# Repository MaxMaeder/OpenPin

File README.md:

# OpenPin

OpenPin is an open-source project which lets you use your Ai Pin after Humane bricked them. You can install it in a few clicks & without any ADB certs!

## Installing OpenPin

Please see [OpenPin.org](https://openpin.org) for installation and usage instructions.

## Building a Interposer

### Bill of Materials

| Qty | Name              | Where to Buy                                      |
| --- | ----------------- | ------------------------------------------------- |
| 4   | M2x8mm Hex Screws | [Amazon](https://www.amazon.com/dp/B094NVN97P)    |
| 4   | M2 Hex Locknuts   | [Amazon](https://www.amazon.com/dp/B07L2W3QX3)    |
| 4   | Small Magnets     | [Amazon](https://www.amazon.com/dp/B0936M3WPK)    |
| 1   | Micro-USB Port    | [DigiKey](https://www.digikey.com/short/t2z9zr7h) |
| 1   | Pogo-Pin Assembly | [DigiKey](https://www.digikey.com/short/dm33vmd2) |

If you order the PCB with the USB-port already soldered (as in the instructions below) you do **NOT** need to buy the 'Micro-USB Port' part.

### Tools Required

| Name                | Where to Buy                                   |
| ------------------- | ---------------------------------------------- |
| 1.5mm Hex Driver    | Inc. with Screws                               |
| 4mm Nut Driver      | [Amazon](https://www.amazon.com/dp/B0009OIJMI) |
| T27 TORX Hex Driver | [Amazon](https://www.amazon.com/dp/B005G3B4MO) |

You will also need soldering tools and a 3D printer, depending on how much you choose to do yourself (versus using a service).

1. Order the PCBs

The following instructions are for if you want to buy the PCBs with the surface mount USB port already soldered.

> These instructions are for JLCPCB. I don't have any affiliation, I just like them.

**Upload gerbers**

- Download the [pin-interposer.zip](interposer/pcb/production/pin-interposer.zip) (the zipped Gerber files)
- Take `pin-interposer.zip`, go to [JLCPCB.com](https://jlcpcb.com), and simply upload into the file dropbox

**Set PCB details**

- The only setting you need to change is toggling on 'PCB Assembly'
- Click next, confirm you see the PCB in the preview, then click next again

**Upload assembly files**

- Download [bom.csv](interposer/pcb/production/bom.csv) and [positions.csv](interposer/pcb/production/positions.csv)
- Upload `bom.csv` into the left dropbox & `positions.csv` into the right, then click next

**Set parts to assemble**

- Click the search icon across from J1, enter `10118193-0001LF`, and search & select it
- Leave the other rows alone
- Click next, it will ask if you are sure you don't want to assemble the other rows, click confirm

**Click through rest of process and check out!**

2. 3D-print plastic parts

- Download the two 3D models: [Pin-Base.stl](interposer/prints/production/Pin-Base.stl) and [Pin-Cradle.stl](interposer/prints/production/Pin-Cradle.stl)
- Print with 0.2mm quality or better in PLA

3. Solder the pogo-pins

- Push the pins of the part into the 4 matching holes on the board<br>
  **Make sure the part is on the same face of the board as the USB port!**
- Solder one pin to start with, make sure its flush with the board and perfectly vertical<br>
  _If not soldered correctly, reheat the solder joint and adjust._
- Solder the remaining pins

4. Final assembly

**Putting the parts together**

- Put the Pin Base down on a table
- Press the PCB into the matching recess (it should be fairly obvious how it fits)
- Place the Pin Cradle overtop of this assembly, aligning it so the pogo pins protrude through the hole

**Screwing everything in**

- Feed the four M2 screw through the holes in top, hand-tighten on nuts
- Use the 1.5mm Hex Driver and 4mm Nut Driver to tighten everything up

**Install magnets**

> **⚠️ It's really important you get the orientation of the magnets correct!**

- Place four magnets on the underside of AI Pin like so:

- Mark the exposed face of each magnet with a sharpie
- Being careful not to get mixed up, transfer each magnet to the corresponding hole on the Pin Cradle, **sharpie-side down**<br>
  **Again, make sure its in the correct hole & in correct orientation!!**
- Depending on your printer tolerances, the magnet may be too hard to push into the hole
  - Use the T27 TORX Hex Driver to file the hole until it fits
  - The driver works great for actually pushing the magnet into the hole, too

5. Enjoy & move on to installing client!

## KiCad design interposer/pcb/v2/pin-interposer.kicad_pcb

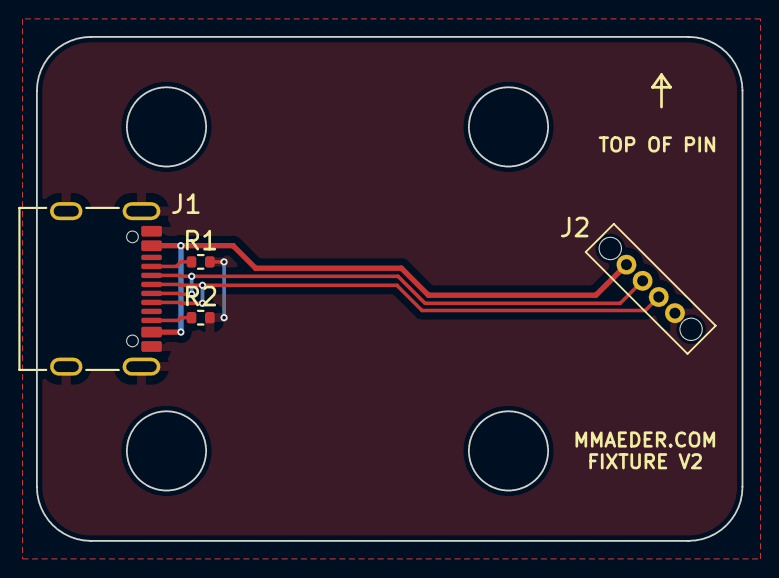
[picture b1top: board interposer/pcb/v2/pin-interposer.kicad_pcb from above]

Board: 2 copper layers, 39.2 x 28.0 mm, 4 parts (0 on the bottom side), 6 nets.

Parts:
J1: GT-USB-7010AN; USB-SMD_GT-USB-7010AN
J2: Conn_01x04_Pin; 854-22-004-10-001101
R1, R2: 5K1; R_0402_1005Metric

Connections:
/D+: J1.A6 (D+), J1.B6 (D+), J2.3
/D-: J1.A7 (D-), J1.B7 (D-), J2.2
GND: J1.A1 (GND), J1.A12 (GND), J1.S1 (SHIELD), J2.4, R1.2, R2.2
unnamed: J1.A5 (CC1), R1.1
unnamed: J1.B5 (CC2), R2.1
VBUS: J1.A4 (VBUS), J1.A9 (VBUS), J2.1

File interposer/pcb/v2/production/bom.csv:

Designator,Footprint,Quantity,Value,LCSC Part #
J1,USB-SMD_GT-USB-7010AN,1,GT-USB-7010AN,
J2,854-22-004-10-001101,1,Conn_01x04_Pin,
"R1, R2",0402,2,5K1,

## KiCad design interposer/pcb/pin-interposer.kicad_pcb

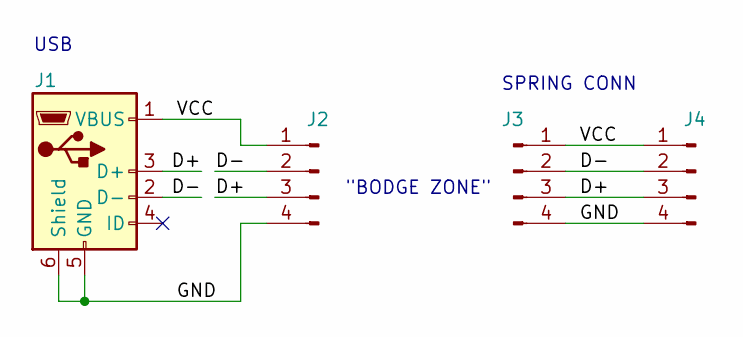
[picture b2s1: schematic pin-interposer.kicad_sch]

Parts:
J1: USB_B_Mini; USB_Micro-B_Amphenol_10118193-0001LF_Horizontal
J2, J3: Conn_01x04_Pin; 4-smd-pads
J4: Conn_01x04_Pin; 854-22-004-10-001101

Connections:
/D+: J1.3 (D+), J2.3, J3.3, J4.3
/D-: J1.2 (D-), J2.2, J3.2, J4.2
/GND: J1.5 (GND), J1.6 (Shield), J2.4, J3.4, J4.4
/VCC: J1.1 (VBUS), J2.1, J3.1, J4.1

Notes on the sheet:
USB
"BODGE ZONE"
SPRING CONN

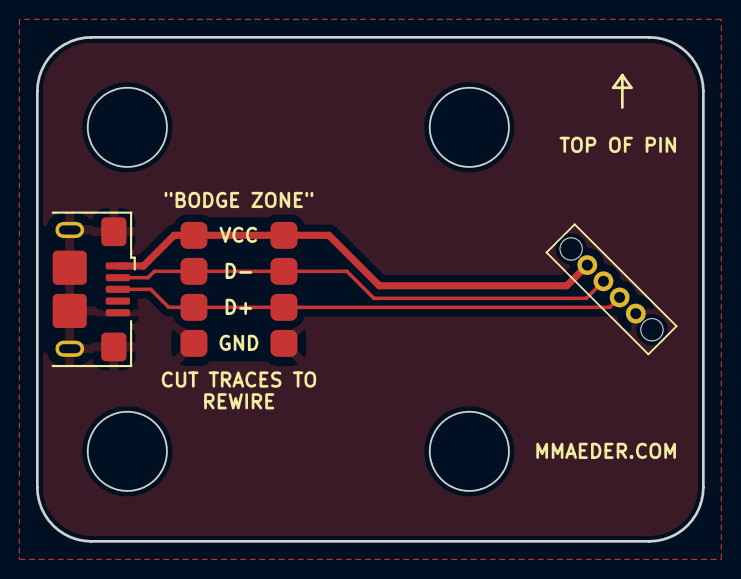
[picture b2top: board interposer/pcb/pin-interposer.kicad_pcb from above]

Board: 2 copper layers, 37.0 x 28.0 mm, 4 parts (0 on the bottom side), 4 nets.

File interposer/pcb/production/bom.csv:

Designator,Footprint,Quantity,Value,LCSC Part #
J1,USB_Micro-B_Amphenol_10118193-0001LF_Horizontal,1,USB_B_Mini,
"J2, J3",4-smd-pads,2,Conn_01x04_Pin,
J4,854-22-004-10-001101,1,Conn_01x04_Pin,

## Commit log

2025-03-13 Init daemon
2025-03-13 Restructure
2025-03-13 Improve long press detection
2025-03-13 Simplify/improve gestures
2025-03-13 Input reader only read from touchpad
2025-03-13 ProcessManager prototype
2025-03-14 Speech works
2025-03-14 Audio effects
2025-03-14 Add other files
2025-03-14 Readme
2025-03-14 Better docs
2025-03-14 Fix missing perm
2025-03-15 Fix small things
2025-03-15 Add camera capture, cancel audio playback
2025-03-15 Davis "works"
2025-03-15 Refine assistant
2025-03-15 Fix image stuff
2025-03-16 Add interposer, AI client files files + directions
2025-03-16 Add 'skip to'
2025-03-16 Line break
2025-03-16 Server init!
2025-03-18 Init
2025-03-18 Import components
2025-03-18 Add .idea stuff
2025-03-18 Rename text
2025-03-19 Optimizations
2025-03-19 Sort of fix I guess
2025-03-19 Further clean up styling stuff, add icons
2025-03-19 Fix ui configs, add audio
2025-03-21 Camera stuff, reorg
2025-03-21 Clean up camera stuff
2025-03-22 More camera, mic stuff
2025-03-22 Clean up permission handling stuff
2025-03-23 Add daemon
2025-03-23 Davis sorta re-implemented
2025-03-23 Fix process errors, location + batt + id, etc
2025-03-23 Rm local properties
2025-03-24 Server is docker container!
2025-03-24 Server translate support
2025-03-25 Translate support in app
2025-03-26 Move server to firebase auth
2025-03-26 Remove old endpoints
2025-03-26 Rough tab impl
2025-03-27 Updates to routing/state
2025-03-27 Reorganize device
2025-03-27 Move settings; broken
2025-03-28 Frontend prototype done
2025-03-29 Clean up stuff
2025-03-29 Add device pairing endpoint
2025-03-30 DB device 'content'
2025-03-31 Client 'content' support
2025-04-01 Fix assistant, add captures, add auth val
2025-04-01 Rename some stuff
2025-04-01 Device loading
2025-04-01 Update device settings
2025-04-01 Fix settings validation
2025-04-01 diy function calling
2025-04-02 Camera compression, update audio stuff
2025-04-02 Move audio assets
2025-04-02 Add audio assets
2025-04-03 Gesture Interpreter init
2025-04-03 New gesture stuff done!
2025-04-03 Hand depth support (go back)
2025-04-04 QR code device linking
2025-04-04 Make sure we're paired before running actions
2025-04-04 Better location service, refactor daemon
2025-04-04 Rename package
2025-04-04 Rm others
2025-04-05 Fix sleep with camera
2025-04-05 Kind of crappy home view
2025-04-05 Backend updates
2025-04-06 Fix sleep
2025-04-11 Start better media gallery
2025-04-11 Clean up lightbox
2025-04-11 Finish lightbox
2025-04-11 Lightbox on messages page
2025-04-11 Reword select, tab layout cleanup
2025-04-11 Navigate to page on link
2025-04-12 Rotate video, rename daemon
2025-04-12 New audio
2025-04-13 Disable non implemented settings
2025-04-13 Update password reqs
2025-04-13 Clean up voice handlers/audio stuff
2025-04-14 Rework davis
2025-04-14 Better error handling, gesture fixes
2025-04-14 Language model choice fixes
2025-04-14 Fix settings updates, add notes
2025-04-14 Handle no speech recognized
2025-04-14 Clean up translate voice upload
2025-04-14 Fix message image attachment
2025-04-14 Fix naming issue
2025-04-15 Clean up small server things
2025-04-15 Handle capture errors
2025-04-16 Finish up device settings stuff
2025-04-17 Fix db massive oops
2025-04-17 Improve default prompt
2025-04-18 Fix issue with re-pairing device
2025-04-19 Improve grok "sexy mode"
2025-04-19 Oop (2)
2025-04-23 Streaming init
2025-04-23 Geolocate caching
2025-04-24 Podcast server init
2025-04-24 Client podcast test
2025-04-25 V2 interposer PCB
2025-04-25 Reorg interposer 3d models
2025-04-25 Init ogg streaming
2025-04-25 Deerfield beach
2025-04-27 Update PCB 3d model
2025-04-27 V2 prints done
2025-04-27 Models update for V2
2025-04-28 Init rough new db
2025-04-28 Device content done
2025-04-28 Finish adding providers/repos
2025-04-29 Local DB works
2025-04-29 Working dev script
2025-04-30 Home location overflow, location backoff
2025-05-04 Updated search.ts to use Brave search (https://api-dashboard.search.brave.com/app/documentation/web-search) if it finds an empty Bing key in the search service. The original format for results is pre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
2025-05-14 Simplify dev script
2025-05-14 Very rough new auth
2025-05-26 Centralize volume multiplier
2025-05-27 Prepare legal things
